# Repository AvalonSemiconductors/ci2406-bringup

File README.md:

# ci2406-bringup
Bring-up of CI2406 multi-project die.

[Documentation](https://avalonsemiconductors.github.io/CI2406/index.html)

[Tapeout repo](https://github.com/rejunity/ci2406-rej-pommedeterrible-tholin)

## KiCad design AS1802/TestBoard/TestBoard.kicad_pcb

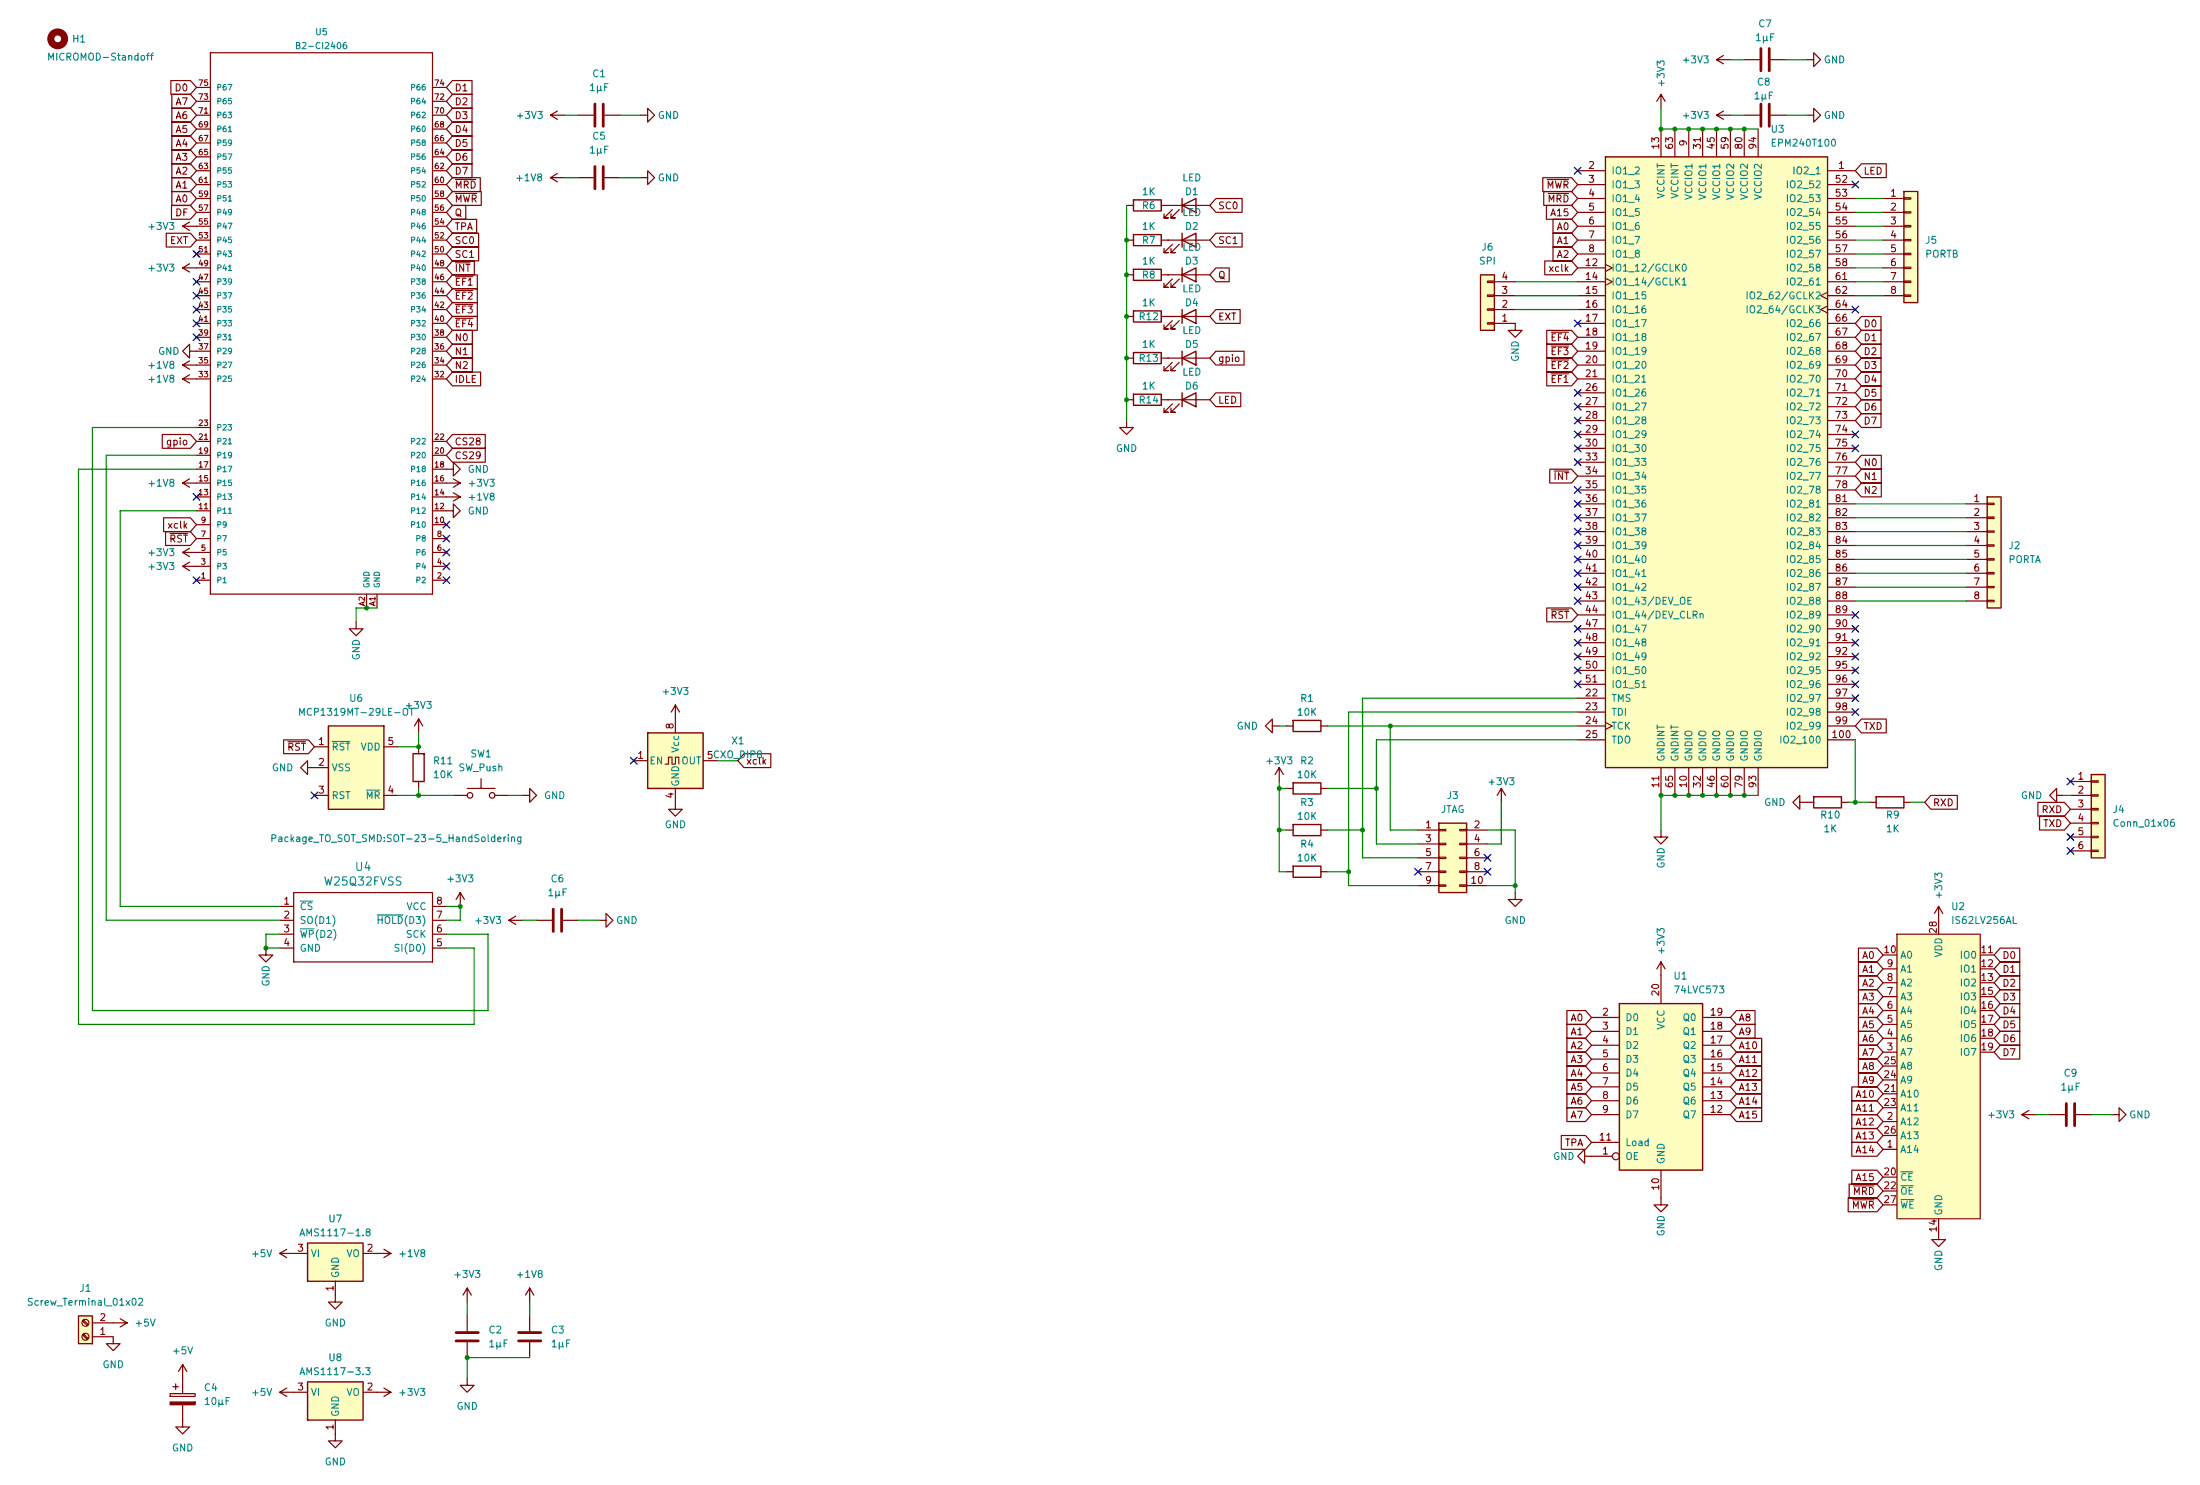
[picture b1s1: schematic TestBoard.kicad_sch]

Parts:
C1, C2, C3, C5, C6, C7, C8, C9: 1µF; C_0805_2012Metric_Pad1.18x1.45mm_HandSolder
C4: 10µF; CP_Radial_D4.0mm_P2.00mm
D1, D2, D3, D4, D5, D6: LED; LED_1206_3216Metric_Pad1.42x1.75mm_HandSolder
H1: MICROMOD-Standoff; MicroMod-Standoff
J1: Screw_Terminal_01x02; TerminalBlock_bornier-2_P5.08mm
J2: PORTA; PinHeader_1x08_P2.54mm_Vertical
J3: JTAG; PinHeader_2x05_P2.54mm_Vertical
J4: Conn_01x06; PinSocket_1x06_P2.54mm_Vertical
J5: PORTB; PinHeader_1x08_P2.54mm_Vertical
J6: SPI; PinHeader_1x04_P2.54mm_Vertical
R1, R2, R3, R4, R11: 10K; R_1206_3216Metric_Pad1.30x1.75mm_HandSolder
R6, R7, R8, R9, R10, R12, R13, R14: 1K; R_1206_3216Metric_Pad1.30x1.75mm_HandSolder
SW1: SW_Push; SW_PUSH_6mm
U1: 74LVC573; SO-20_12.8x7.5mm_P1.27mm
U2: IS62LV256AL; TSOP-I-28_11.8x8mm_P0.55mm-weird-pin-order
U3: EPM240T100; LQFP-100_14x14mm_P0.5mm
U4: W25Q32FVSS; DIP-8_W7.62mm; Part # W25Q32JVSSIQ
U5: B2-CI2406; M.2-CONNECTOR-E
U6: MCP1319MT-29LE-OT; SOT-23-5_HandSoldering
U7: AMS1117-1.8; SOT-223-3_TabPin2
U8: AMS1117-3.3; SOT-223-3_TabPin2
X1: CXO_DIP8; Oscillator_DIP-8

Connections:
+1V8: C3.2, C5.1, U5.14, U5.15, U5.33 (P25), U5.35 (P27), U7.2 (VO)
+3V3: C1.1, C2.2, C6.1, C7.1, C8.1, C9.1, J3.4, R2.2, R3.2, R4.2, R11.2, U1.20 (VCC), U2.28 (VDD), U3.9 (VCCIO1), U3.13 (VCCINT), U3.31 (VCCIO1), U3.45 (VCCIO1), U3.59 (VCCIO2), U3.63 (VCCINT), U3.80 (VCCIO2), U3.94 (VCCIO2), U4.7 (~HOLD(D3)), U4.8 (VCC), U5.3, U5.5, U5.16, U5.49 (P41), U5.55 (P47), U6.5 (VDD), U8.2 (VO), X1.8 (Vcc)
+5V: C4.1, J1.2, U7.3 (VI), U8.3 (VI)
A0: U1.2 (D0), U2.10 (A0), U3.6 (IO1_6), U5.59 (P51)
A1: U1.3 (D1), U2.9 (A1), U3.7 (IO1_7), U5.61 (P53)
A2: U1.4 (D2), U2.8 (A2), U3.8 (IO1_8), U5.63 (P55)
A3: U1.5 (D3), U2.7 (A3), U5.65 (P57)
A4: U1.6 (D4), U2.6 (A4), U5.67 (P59)
A5: U1.7 (D5), U2.5 (A5), U5.69 (P61)
A6: U1.8 (D6), U2.4 (A6), U5.71 (P63)
A7: U1.9 (D7), U2.3 (A7), U5.73 (P65)
A8: U1.19 (Q0), U2.25 (A8)
A9: U1.18 (Q1), U2.24 (A9)
A10: U1.17 (Q2), U2.21 (A10)
A11: U1.16 (Q3), U2.23 (A11)
A12: U1.15 (Q4), U2.2 (A12)
A13: U1.14 (Q5), U2.26 (A13)
A14: U1.13 (Q6), U2.1 (A14)
A15: U1.12 (Q7), U2.20 (~CE), U3.5 (IO1_5)
CS28: U5.22
CS29: U5.20
D0: U2.11 (IO0), U3.66 (IO2_66), U5.75 (P67)
D1: U2.12 (IO1), U3.67 (IO2_67), U5.74 (P66)
D2: U2.13 (IO2), U3.68 (IO2_68), U5.72 (P64)
D3: U2.15 (IO3), U3.69 (IO2_69), U5.70 (P62)
D4: U2.16 (IO4), U3.70 (IO2_70), U5.68 (P60)
D5: U2.17 (IO5), U3.71 (IO2_71), U5.66 (P58)
D6: U2.18 (IO6), U3.72 (IO2_72), U5.64 (P56)
D7: U2.19 (IO7), U3.73 (IO2_73), U5.62 (P54)
DF: U5.57 (P49)
EXT: D4.2 (A), U5.53 (P45)
GND: C1.2, C2.1, C3.1, C4.2, C5.2, C6.2, C7.2, C8.2, C9.2, J1.1, J3.2, J3.10, J4.2, J6.1, R1.2, R6.2, R7.2, R8.2, R10.2, R12.2, R13.2, R14.2, SW1.2, U1.1 (OE), U1.10 (GND), U2.14 (GND), U3.10 (GNDIO), U3.11 (GNDINT), U3.32 (GNDIO), U3.46 (GNDIO), U3.60 (GNDIO), U3.65 (GNDINT), U3.79 (GNDIO), U3.93 (GNDIO), U4.3 (~WP(D2)), U4.4 (GND), U5.12, U5.18, U5.37 (P29), U5.A1 (GND), U5.A2 (GND), U6.2 (VSS), U7.1 (GND), U8.1 (GND), X1.4 (GND)
IDLE: U5.32 (P24)
LED: D6.2 (A), U3.1 (IO2_1)
N0: U3.76 (IO2_76), U5.38 (P30)
N1: U3.77 (IO2_77), U5.36 (P28)
N2: U3.78 (IO2_78), U5.34 (P26)
unnamed: D1.1 (K), R6.1
unnamed: D2.1 (K), R7.1
unnamed: D3.1 (K), R8.1
unnamed: D4.1 (K), R12.1
unnamed: D5.1 (K), R13.1
unnamed: D6.1 (K), R14.1
unnamed: J2.1, U3.81 (IO2_81)
unnamed: J2.2, U3.82 (IO2_82)
unnamed: J2.3, U3.83 (IO2_83)
unnamed: J2.4, U3.84 (IO2_84)
unnamed: J2.5, U3.85 (IO2_85)
unnamed: J2.6, U3.86 (IO2_86)
unnamed: J2.7, U3.87 (IO2_87)
unnamed: J2.8, U3.88 (IO2_88)
unnamed: J3.1, R1.1, U3.24 (TCK)
unnamed: J3.3, R2.1, U3.25 (TDO)
unnamed: J3.5, R3.1, U3.22 (TMS)
unnamed: J3.9, R4.1, U3.23 (TDI)
unnamed: J5.1, U3.53 (IO2_53)
unnamed: J5.2, U3.54 (IO2_54)
unnamed: J5.3, U3.55 (IO2_55)
unnamed: J5.4, U3.56 (IO2_56)
unnamed: J5.5, U3.57 (IO2_57)
unnamed: J5.6, U3.58 (IO2_58)
unnamed: J5.7, U3.61 (IO2_61)
unnamed: J5.8, U3.62 (IO2_62/GCLK2)
unnamed: J6.2, U3.16 (IO1_16)
unnamed: J6.3, U3.15 (IO1_15)
unnamed: J6.4, U3.14 (IO1_14/GCLK1)
unnamed: R9.2, R10.1, U3.100 (IO2_100)
unnamed: U4.6 (SCK), U5.23
unnamed: U4.5 (SI(D0)), U5.17
unnamed: U4.2 (SO(D1)), U5.19
unnamed: U4.1 (~CS), U5.11
unnamed: R11.1, SW1.1, U6.4 (~MR)
Q: D3.2 (A), U5.56 (P48)
RXD: J4.3, R9.1
SC0: D1.2 (A), U5.52 (P44)
SC1: D2.2 (A), U5.50 (P42)
TPA: U1.11 (Load), U5.54 (P46)
TXD: J4.4, U3.99 (IO2_99)
gpio: D5.2 (A), U5.21
xclk: U3.12 (IO1_12/GCLK0), U5.9, X1.5 (OUT)
~EF1: U3.21 (IO1_21), U5.46 (P38)
~EF2: U3.20 (IO1_20), U5.44 (P36)
~EF3: U3.19 (IO1_19), U5.42 (P34)
~EF4: U3.18 (IO1_18), U5.40 (P32)
~INT: U3.34 (IO1_34), U5.48 (P40)
~MRD: U2.22 (~OE), U3.4 (IO1_4), U5.60 (P52)
~MWR: U2.27 (~WE), U3.3 (IO1_3), U5.58 (P50)
~RST: U3.44 (IO1_44/DEV_CLRn), U5.7, U6.1 (~RST)

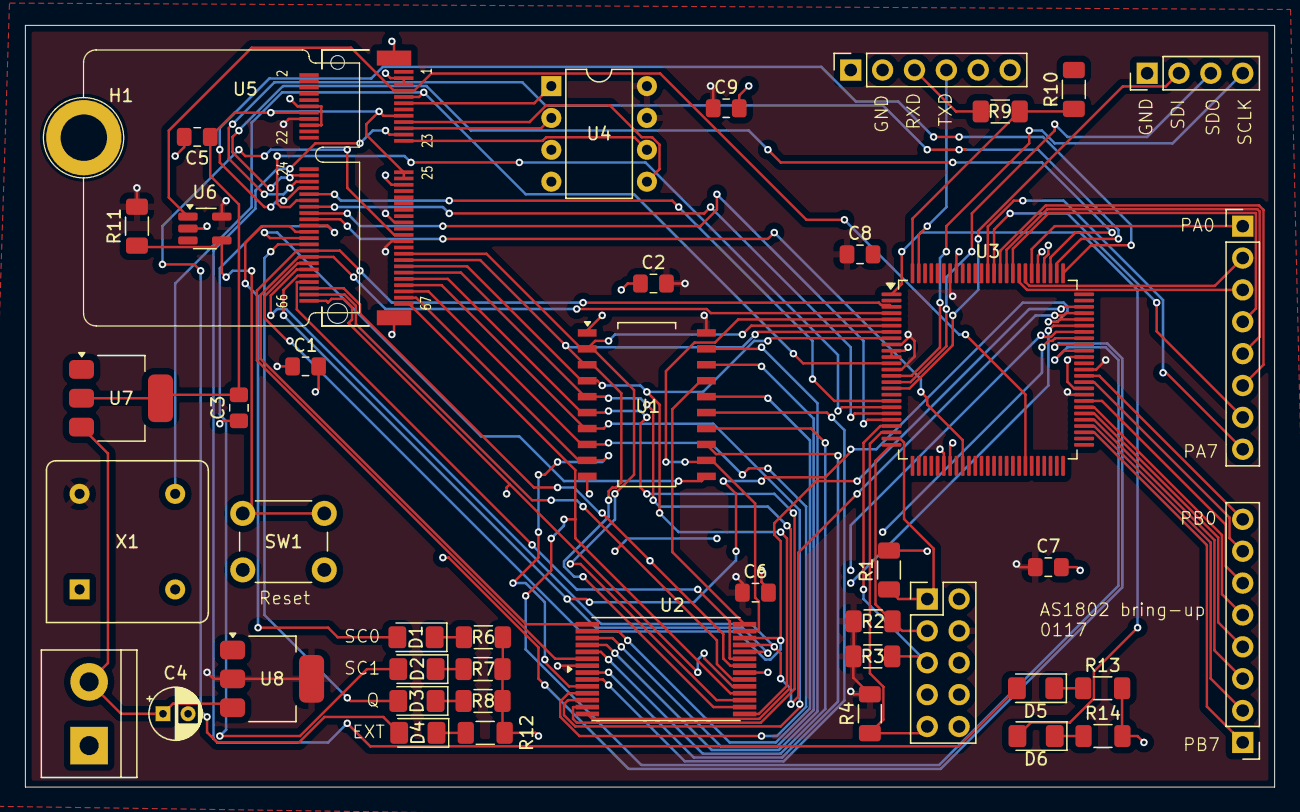
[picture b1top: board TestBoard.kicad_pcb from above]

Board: 4 copper layers, 99.6 x 60.7 mm, 45 parts (0 on the bottom side), 84 nets.

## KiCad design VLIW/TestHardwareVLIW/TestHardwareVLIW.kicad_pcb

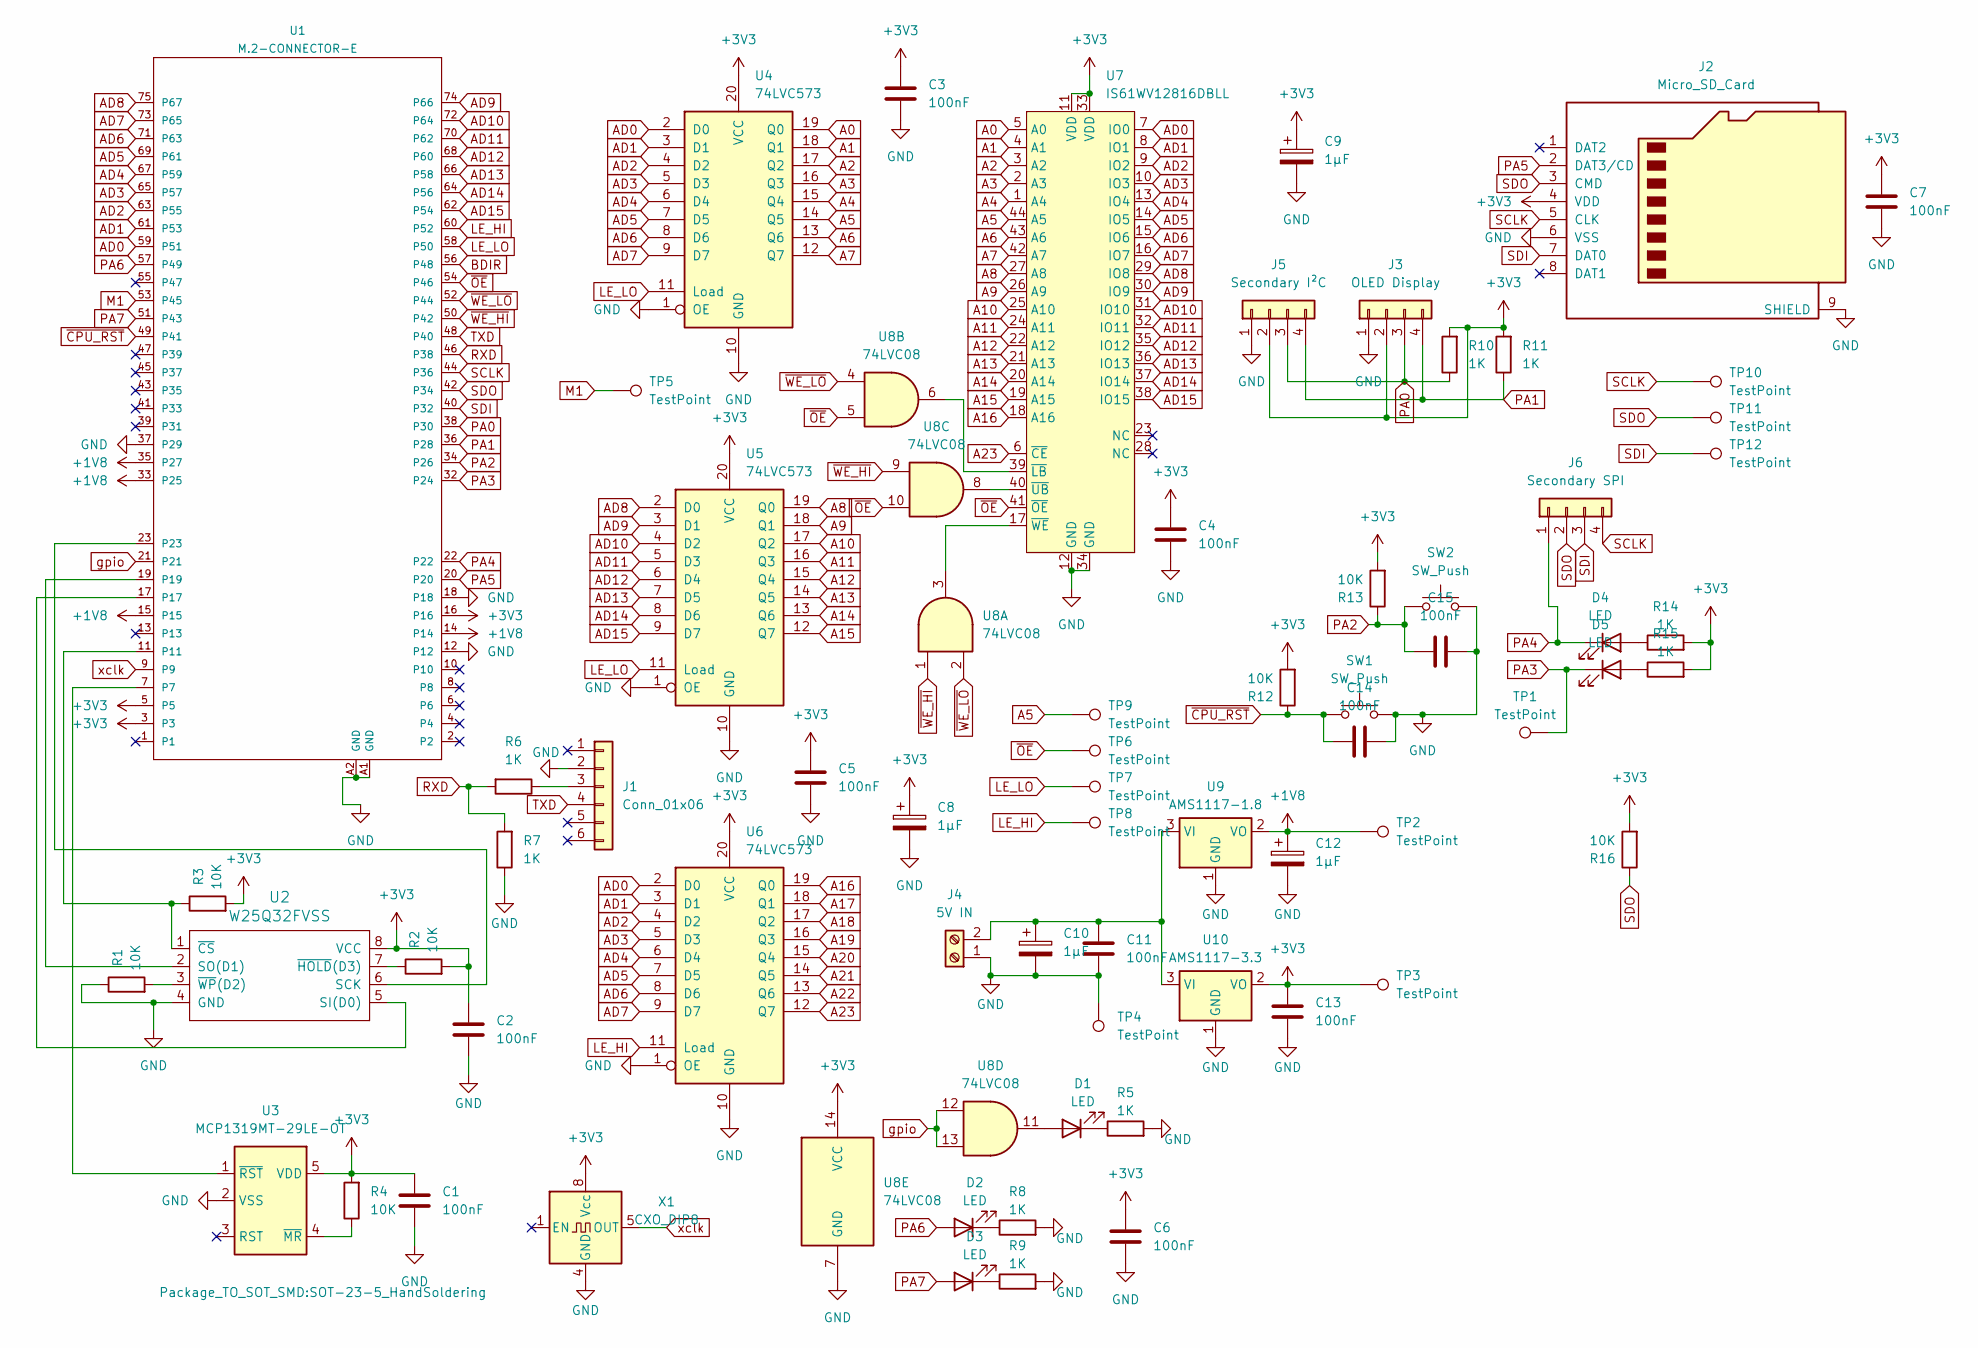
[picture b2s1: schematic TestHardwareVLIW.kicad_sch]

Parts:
C1, C2, C3, C4, C5, C6, C7, C11, C13, C14, C15: 100nF; C_0805_2012Metric_Pad1.18x1.45mm_HandSolder
C8, C9, C10, C12: 1µF; CP_Radial_D4.0mm_P2.00mm
D1, D2, D3, D4, D5: LED; LED_1206_3216Metric_Pad1.42x1.75mm_HandSolder
J1: Conn_01x06; PinSocket_1x06_P2.54mm_Vertical
J2: Micro_SD_Card; microSD_HC_Hirose_DM3AT-SF-PEJM5
J3: OLED Display; PinSocket_1x04_P2.54mm_Vertical
J4: 5V IN; TerminalBlock_bornier-2_P5.08mm
J5: Secondary I²C; PinSocket_1x04_P2.54mm_Vertical
J6: Secondary SPI; PinSocket_1x04_P2.54mm_Vertical
R1, R2, R3, R12, R13, R16: 10K; R_1206_3216Metric_Pad1.30x1.75mm_HandSolder; Part # RC0805FR-0710KL
R4: 10K; R_1206_3216Metric_Pad1.30x1.75mm_HandSolder
R5, R6, R7, R8, R9, R10, R11, R14, R15: 1K; R_1206_3216Metric_Pad1.30x1.75mm_HandSolder
SW1, SW2: SW_Push; SW_PUSH_6mm
TP1, TP2, TP3, TP4, TP5, TP6, TP7, TP8, TP9, TP10, TP11, TP12: TestPoint; TestPoint_Pad_D1.0mm
U1: M.2-CONNECTOR-E
U2: W25Q32FVSS; DIP-8_W7.62mm; Part # W25Q32JVSSIQ
U3: MCP1319MT-29LE-OT; SOT-23-5_HandSoldering
U4, U5, U6: 74LVC573; TSSOP-20_4.4x6.5mm_P0.65mm
U7: IS61WV12816DBLL; TSOP-II-44_10.16x18.41mm_P0.8mm
U8: 74LVC08; SO-14_3.9x8.65mm_P1.27mm
U9: AMS1117-1.8; SOT-223-3_TabPin2
U10: AMS1117-3.3; SOT-223-3_TabPin2
X1: CXO_DIP8; Oscillator_DIP-8

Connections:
+1V8: C12.1, TP2.1, U1.14, U1.15, U1.33 (P25), U1.35 (P27), U9.2 (VO)
+3V3: C1.1, C2.1, C3.1, C4.1, C5.1, C6.1, C7.1, C8.1, C9.1, C13.1, J2.4 (VDD), J3.2, J5.2, R2.2, R3.2, R4.2, R10.2, R11.2, R12.2, R13.2, R14.2, R15.2, R16.2, TP3.1, U1.3, U1.5, U1.16, U2.8 (VCC), U3.5 (VDD), U4.20 (VCC), U5.20 (VCC), U6.20 (VCC), U7.11 (VDD), U7.33 (VDD), U8.14 (VCC), U10.2 (VO), X1.8 (Vcc)
A0: U4.19 (Q0), U7.5 (A0)
A1: U4.18 (Q1), U7.4 (A1)
A2: U4.17 (Q2), U7.3 (A2)
A3: U4.16 (Q3), U7.2 (A3)
A4: U4.15 (Q4), U7.1 (A4)
A5: TP9.1, U4.14 (Q5), U7.44 (A5)
A6: U4.13 (Q6), U7.43 (A6)
A7: U4.12 (Q7), U7.42 (A7)
A8: U5.19 (Q0), U7.27 (A8)
A9: U5.18 (Q1), U7.26 (A9)
A10: U5.17 (Q2), U7.25 (A10)
A11: U5.16 (Q3), U7.24 (A11)
A12: U5.15 (Q4), U7.22 (A12)
A13: U5.14 (Q5), U7.21 (A13)
A14: U5.13 (Q6), U7.20 (A14)
A15: U5.12 (Q7), U7.19 (A15)
A16: U6.19 (Q0), U7.18 (A16)
A17: U6.18 (Q1)
A18: U6.17 (Q2)
A19: U6.16 (Q3)
A20: U6.15 (Q4)
A21: U6.14 (Q5)
A22: U6.13 (Q6)
A23: U6.12 (Q7), U7.6 (~CE)
AD0: U1.59 (P51), U4.2 (D0), U6.2 (D0), U7.7 (IO0)
AD1: U1.61 (P53), U4.3 (D1), U6.3 (D1), U7.8 (IO1)
AD2: U1.63 (P55), U4.4 (D2), U6.4 (D2), U7.9 (IO2)
AD3: U1.65 (P57), U4.5 (D3), U6.5 (D3), U7.10 (IO3)
AD4: U1.67 (P59), U4.6 (D4), U6.6 (D4), U7.13 (IO4)
AD5: U1.69 (P61), U4.7 (D5), U6.7 (D5), U7.14 (IO5)
AD6: U1.71 (P63), U4.8 (D6), U6.8 (D6), U7.15 (IO6)
AD7: U1.73 (P65), U4.9 (D7), U6.9 (D7), U7.16 (IO7)
AD8: U1.75 (P67), U5.2 (D0), U7.29 (IO8)
AD9: U1.74 (P66), U5.3 (D1), U7.30 (IO9)
AD10: U1.72 (P64), U5.4 (D2), U7.31 (IO10)
AD11: U1.70 (P62), U5.5 (D3), U7.32 (IO11)
AD12: U1.68 (P60), U5.6 (D4), U7.35 (IO12)
AD13: U1.66 (P58), U5.7 (D5), U7.36 (IO13)
AD14: U1.64 (P56), U5.8 (D6), U7.37 (IO14)
AD15: U1.62 (P54), U5.9 (D7), U7.38 (IO15)
BDIR: U1.56 (P48)
GND: C1.2, C2.2, C3.2, C4.2, C5.2, C6.2, C7.2, C8.2, C9.2, C10.2, C11.2, C12.2, C13.2, C14.1, C15.1, J1.2, J2.6 (VSS), J2.9 (SHIELD), J3.1, J4.1, J5.1, R1.1, R5.2, R7.1, R8.2, R9.2, SW1.2, SW2.2, TP4.1, U1.12, U1.18, U1.37 (P29), U1.A1 (GND), U1.A2 (GND), U2.4 (GND), U3.2 (VSS), U4.1 (OE), U4.10 (GND), U5.1 (OE), U5.10 (GND), U6.1 (OE), U6.10 (GND), U7.12 (GND), U7.34 (GND), U8.7 (GND), U9.1 (GND), U10.1 (GND), X1.4 (GND)
LE_HI: TP8.1, U1.60 (P52), U6.11 (Load)
LE_LO: TP7.1, U1.58 (P50), U4.11 (Load), U5.11 (Load)
M1: TP5.1, U1.53 (P45)
unnamed: D1.2 (A), U8.11
unnamed: D1.1 (K), R5.1
unnamed: D2.1 (K), R8.1
unnamed: D3.1 (K), R9.1
unnamed: D4.2 (A), R14.1
unnamed: D5.2 (A), R15.1
unnamed: J1.3, R6.1
unnamed: C10.1, C11.1, J4.2, U9.3 (VI), U10.3 (VI)
unnamed: U1.7, U3.1 (~RST)
unnamed: R3.1, U1.11, U2.1 (~CS)
unnamed: U1.17, U2.5 (SI(D0))
unnamed: U1.19, U2.2 (SO(D1))
unnamed: U1.23, U2.6 (SCK)
unnamed: R2.1, U2.7 (~HOLD(D3))
unnamed: R1.2, U2.3 (~WP(D2))
unnamed: R4.1, U3.4 (~MR)
unnamed: U7.39 (~LB), U8.6
unnamed: U7.40 (~UB), U8.8
unnamed: U7.17 (~WE), U8.3
PA0: J3.3, J5.3, R10.1, U1.38 (P30)
PA1: J3.4, J5.4, R11.1, U1.36 (P28)
PA2: C15.2, R13.1, SW2.1, U1.34 (P26)
PA3: D5.1 (K), TP1.1, U1.32 (P24)
PA4: D4.1 (K), J6.1, U1.22
PA5: J2.2 (DAT3/CD), U1.20
PA6: D2.2 (A), U1.57 (P49)
PA7: D3.2 (A), U1.51 (P43)
RXD: R6.2, R7.2, U1.46 (P38)
SCLK: J2.5 (CLK), J6.4, TP10.1, U1.44 (P36)
SDI: J2.7 (DAT0), J6.3, TP12.1, U1.40 (P32)
SDO: J2.3 (CMD), J6.2, R16.1, TP11.1, U1.42 (P34)
TXD: J1.4, U1.48 (P40)
gpio: U1.21, U8.12, U8.13
xclk: U1.9, X1.5 (OUT)
~CPU_RST: C14.2, R12.1, SW1.1, U1.49 (P41)
~OE: TP6.1, U1.54 (P46), U7.41 (~OE), U8.5, U8.10
~WE_HI: U1.50 (P42), U8.1, U8.9
~WE_LO: U1.52 (P44), U8.2, U8.4

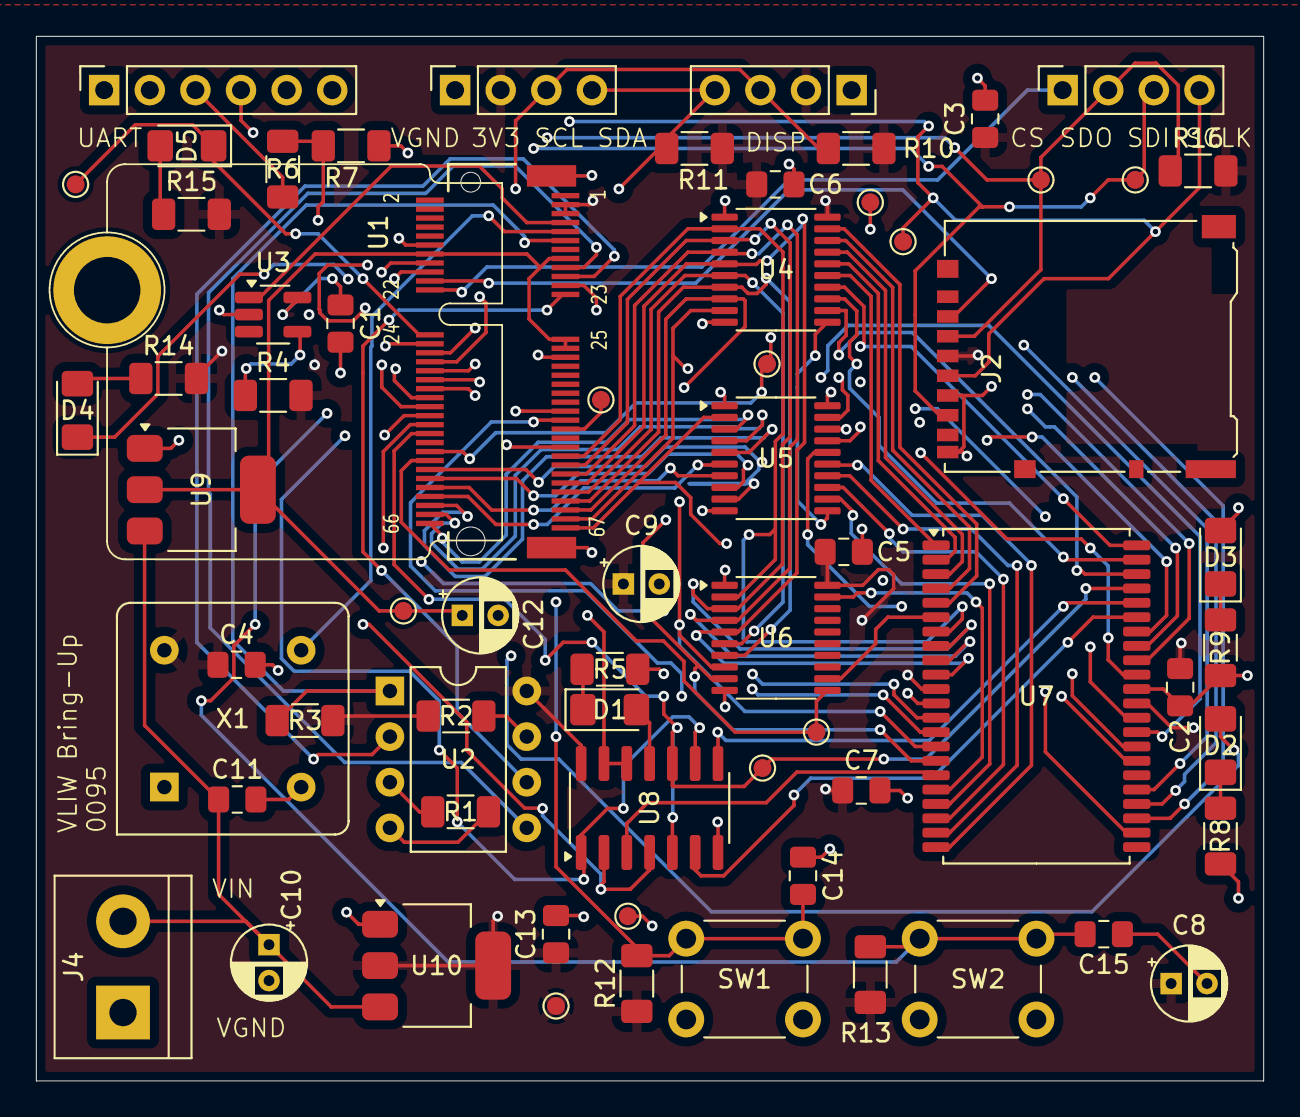
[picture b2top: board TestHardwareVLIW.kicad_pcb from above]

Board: 4 copper layers, 68.3 x 58.2 mm, 67 parts (0 on the bottom side), 78 nets.

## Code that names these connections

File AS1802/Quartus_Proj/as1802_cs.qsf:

# -------------------------------------------------------------------------- #
#
# Copyright (C) 2025  Altera Corporation. All rights reserved.
# Your use of Altera Corporation's design tools, logic functions 
# and other software and tools, and any partner logic 
# functions, and any output files from any of the foregoing 
# (including device programming or simulation files), and any 
# associated documentation or information are expressly subject 
# to the terms and conditions of the Altera Program License 
# Subscription Agreement, the Altera Quartus Prime License Agreement,
# the Altera IP License Agreement, or other applicable license
# agreement, including, without limitation, that your use is for
# the sole purpose of programming logic devices manufactured by
# Altera and sold by Altera or its authorized distributors.  Please
# refer to the Altera Software License Subscription Agreements 
# on the Quartus Prime software download page.
#
# -------------------------------------------------------------------------- #
#
# Quartus Prime
# Version 24.1std.0 Build 1077 03/04/2025 SC Lite Edition
# Date created = 18:14:34  Mai 04, 2025
#
# -------------------------------------------------------------------------- #
#
# Notes:
#
# 1) The default values for assignments are stored in the file:
#		as1802_cs_assignment_defaults.qdf
#    If this file doesn't exist, see file:
#		assignment_defaults.qdf
#
# 2) Intel recommends that you do not modify this file. This
#    file is updated automatically by the Quartus Prime software
#    and any changes you make may be lost or overwritten.
#
# -------------------------------------------------------------------------- #


set_global_assignment -name FAMILY "MAX II"
set_global_assignment -name DEVICE EPM240T100C5
set_global_assignment -name TOP_LEVEL_ENTITY as1802_cs
set_global_assignment -name ORIGINAL_QUARTUS_VERSION 24.1STD.0
set_global_assignment -name PROJECT_CREATION_TIME_DATE "18:14:34  MAI 04, 2025"
set_global_assignment -name LAST_QUARTUS_VERSION "24.1std.0 Lite Edition"
set_global_assignment -name PROJECT_OUTPUT_DIRECTORY output_files
set_global_assignment -name MIN_CORE_JUNCTION_TEMP 0
set_global_assignment -name MAX_CORE_JUNCTION_TEMP 85
set_global_assignment -name DEVICE_FILTER_PACKAGE TQFP
set_global_assignment -name DEVICE_FILTER_PIN_COUNT 100
set_global_assignment -name ERROR_CHECK_FREQUENCY_DIVISOR "-1"
set_global_assignment -name POWER_EXT_SUPPLY_VOLTAGE_TO_REGULATOR 3.3V
set_global_assignment -name VERILOG_FILE cpld.v
set_global_assignment -name AUTO_RESTART_CONFIGURATION OFF
set_global_assignment -name ENABLE_DEVICE_WIDE_RESET ON
set_global_assignment -name ENABLE_OCT_DONE OFF
set_global_assignment -name ENABLE_CONFIGURATION_PINS OFF
set_global_assignment -name ENABLE_BOOT_SEL_PIN OFF
set_global_assignment -name USE_CONFIGURATION_DEVICE ON
set_global_assignment -name RESERVE_ALL_UNUSED_PINS "AS INPUT TRI-STATED WITH WEAK PULL-UP"
set_location_assignment PIN_5 -to A15
set_location_assignment PIN_73 -to D[7]
set_location_assignment PIN_72 -to D[6]
set_location_assignment PIN_71 -to D[5]
set_location_assignment PIN_70 -to D[4]
set_location_assignment PIN_69 -to D[3]
set_location_assignment PIN_68 -to D[2]
set_location_assignment PIN_67 -to D[1]
set_location_assignment PIN_66 -to D[0]
set_location_assignment PIN_18 -to EF_b[3]
set_location_assignment PIN_19 -to EF_b[2]
set_location_assignment PIN_20 -to EF_b[1]
set_location_assignment PIN_21 -to EF_b[0]
set_location_assignment PIN_1 -to LED
set_location_assignment PIN_4 -to MRD_b
set_location_assignment PIN_3 -to MWR_b
set_location_assignment PIN_26 -to N[2]
set_location_assignment PIN_27 -to N[1]
set_location_assignment PIN_28 -to N[0]
set_location_assignment PIN_88 -to PORTA[7]
set_location_assignment PIN_87 -to PORTA[6]
set_location_assignment PIN_86 -to PORTA[5]
set_location_assignment PIN_85 -to PORTA[4]
set_location_assignment PIN_84 -to PORTA[3]
set_location_assignment PIN_83 -to PORTA[2]
set_location_assignment PIN_82 -to PORTA[1]
set_location_assignment PIN_81 -to PORTA[0]
set_location_assignment PIN_53 -to PORTB[7]
set_location_assignment PIN_54 -to PORTB[6]
set_location_assignment PIN_55 -to PORTB[5]
set_location_assignment PIN_56 -to PORTB[4]
set_location_assignment PIN_57 -to PORTB[3]
set_location_assignment PIN_58 -to PORTB[2]
set_location_assignment PIN_61 -to PORTB[1]
set_location_assignment PIN_62 -to PORTB[0]
set_location_assignment PIN_100 -to RXD
set_location_assignment PIN_99 -to TXD
set_location_assignment PIN_14 -to SCK
set_location_assignment PIN_16 -to SDI
set_location_assignment PIN_15 -to SDO
set_location_assignment PIN_8 -to addr[2]
set_location_assignment PIN_7 -to addr[1]
set_location_assignment PIN_6 -to addr[0]
set_location_assignment PIN_34 -to int_b
set_location_assignment PIN_12 -to xclk

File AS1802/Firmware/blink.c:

#include <defs.h>
#include "../Programs/BringUpSample/pgmdata.h"

#define reg_mprj_proj_sel (*(volatile uint32_t*)0x30100004)
#define reg_mprj_counter  (*(volatile uint32_t*)0x30100008)
#define reg_mprj_settings (*(volatile uint32_t*)0x3010000C)

#define START_ADDRESS 0
#define START_X 1
#define START_P 0
#define GATE_TPA 1
#define CS 1

#define MRD (1 << 21)
#define MWR (1 << 22)
#define Q_L (1 << 23)
#define TPA (1 << 24)


void delay(const int d) {
	#ifdef BROKEN_CHIP
	for(int i = 0; i < d >> 2; i++) asm volatile("nop");
	#else
	reg_timer0_config = 0;
	reg_timer0_data = d;
	reg_timer0_config = 1;
	
	reg_timer0_update = 1;
	while (reg_timer0_value > 0) {
		reg_timer0_update = 1;
	}
	#endif
}

uint32_t datal_shadow;

void configure_io_mgmt(uint8_t input) {
	reg_mprj_io_0 = GPIO_MODE_USER_STD_INPUT_PULLDOWN;
	reg_mprj_io_1 = GPIO_MODE_MGMT_STD_OUTPUT;
	reg_mprj_io_2 = GPIO_MODE_MGMT_STD_OUTPUT;
	reg_mprj_io_3 = GPIO_MODE_MGMT_STD_INPUT_PULLUP;
	reg_mprj_io_4 = GPIO_MODE_MGMT_STD_OUTPUT;
	
	reg_mprj_io_5 = GPIO_MODE_MGMT_STD_OUTPUT;
	reg_mprj_io_6 = GPIO_MODE_MGMT_STD_OUTPUT;
	reg_mprj_io_7 = GPIO_MODE_MGMT_STD_OUTPUT;
	reg_mprj_io_8 = GPIO_MODE_MGMT_STD_OUTPUT;
	reg_mprj_io_9 = GPIO_MODE_MGMT_STD_OUTPUT;
	reg_mprj_io_10 = GPIO_MODE_MGMT_STD_OUTPUT;
	reg_mprj_io_11 = GPIO_MODE_MGMT_STD_OUTPUT;
	reg_mprj_io_12 = GPIO_MODE_MGMT_STD_OUTPUT;
	if(input) {
		reg_mprj_io_13 = GPIO_MODE_MGMT_STD_INPUT_PULLUP;
		reg_mprj_io_14 = GPIO_MODE_MGMT_STD_INPUT_PULLUP;
		reg_mprj_io_15 = GPIO_MODE_MGMT_STD_INPUT_PULLUP;
		reg_mprj_io_16 = GPIO_MODE_MGMT_STD_INPUT_PULLUP;
		reg_mprj_io_17 = GPIO_MODE_MGMT_STD_INPUT_PULLUP;
		reg_mprj_io_18 = GPIO_MODE_MGMT_STD_INPUT_PULLUP;
		reg_mprj_io_19 = GPIO_MODE_MGMT_STD_INPUT_PULLUP;
		reg_mprj_io_20 = GPIO_MODE_MGMT_STD_INPUT_PULLUP;
	}else {
		reg_mprj_io_13 = GPIO_MODE_MGMT_STD_OUTPUT;
		reg_mprj_io_14 = GPIO_MODE_MGMT_STD_OUTPUT;
		reg_mprj_io_15 = GPIO_MODE_MGMT_STD_OUTPUT;
		reg_mprj_io_16 = GPIO_MODE_MGMT_STD_OUTPUT;
		reg_mprj_io_17 = GPIO_MODE_MGMT_STD_OUTPUT;
		reg_mprj_io_18 = GPIO_MODE_MGMT_STD_OUTPUT;
		reg_mprj_io_19 = GPIO_MODE_MGMT_STD_OUTPUT;
		reg_mprj_io_20 = GPIO_MODE_MGMT_STD_OUTPUT;
	}
	reg_mprj_io_21 = GPIO_MODE_MGMT_STD_OUTPUT;
	reg_mprj_io_22 = GPIO_MODE_MGMT_STD_OUTPUT;
	reg_mprj_io_23 = GPIO_MODE_MGMT_STD_OUTPUT;
	reg_mprj_io_24 = GPIO_MODE_MGMT_STD_OUTPUT;
	reg_mprj_io_25 = GPIO_MODE_MGMT_STD_OUTPUT;
	reg_mprj_io_26 = GPIO_MODE_MGMT_STD_INPUT_NOPULL;
	reg_mprj_io_27 = GPIO_MODE_MGMT_STD_INPUT_PULLUP;
	reg_mprj_io_28 = GPIO_MODE_MGMT_STD_INPUT_PULLUP;
	reg_mprj_io_29 = GPIO_MODE_MGMT_STD_INPUT_PULLUP;
	reg_mprj_io_30 = GPIO_MODE_MGMT_STD_INPUT_PULLUP;
	reg_mprj_io_31 = GPIO_MODE_MGMT_STD_INPUT_PULLUP;
	reg_mprj_io_32 = GPIO_MODE_MGMT_STD_OUTPUT;
	reg_mprj_io_33 = GPIO_MODE_MGMT_STD_OUTPUT;
	reg_mprj_io_34 = GPIO_MODE_MGMT_STD_OUTPUT;
	reg_mprj_io_35 = GPIO_MODE_MGMT_STD_OUTPUT;
	reg_mprj_io_36 = GPIO_MODE_MGMT_STD_OUTPUT;
	reg_mprj_io_37 = GPIO_MODE_MGMT_STD_OUTPUT;
	
	reg_mprj_datal = datal_shadow = MRD | MWR;
	reg_mprj_datah = 0xFFFFFFFF;
	reg_mprj_xfer = 1;
	while(reg_mprj_xfer == 1);
}

void configure_io_as1802() {
	reg_mprj_io_0 = GPIO_MODE_USER_STD_INPUT_PULLDOWN;
	reg_mprj_io_1 = GPIO_MODE_USER_STD_OUTPUT;
	reg_mprj_io_2 = GPIO_MODE_USER_STD_OUTPUT;
	reg_mprj_io_3 = GPIO_MODE_MGMT_STD_INPUT_PULLUP;
	reg_mprj_io_4 = GPIO_MODE_USER_STD_OUTPUT;
	
	reg_mprj_io_5 = GPIO_MODE_USER_STD_OUTPUT;
	reg_mprj_io_6 = GPIO_MODE_USER_STD_OUTPUT;
	reg_mprj_io_7 = GPIO_MODE_USER_STD_OUTPUT;
	reg_mprj_io_8 = GPIO_MODE_USER_STD_OUTPUT;
	reg_mprj_io_9 = GPIO_MODE_USER_STD_OUTPUT;
	reg_mprj_io_10 = GPIO_MODE_USER_STD_OUTPUT;
	reg_mprj_io_11 = GPIO_MODE_USER_STD_OUTPUT;
	reg_mprj_io_12 = GPIO_MODE_USER_STD_OUTPUT;
	reg_mprj_io_13 = GPIO_MODE_USER_STD_BIDIRECTIONAL;
	reg_mprj_io_14 = GPIO_MODE_USER_STD_BIDIRECTIONAL;
	reg_mprj_io_15 = GPIO_MODE_USER_STD_BIDIRECTIONAL;
	reg_mprj_io_16 = GPIO_MODE_USER_STD_BIDIRECTIONAL;
	reg_mprj_io_17 = GPIO_MODE_USER_STD_BIDIRECTIONAL;
	reg_mprj_io_18 = GPIO_MODE_USER_STD_BIDIRECTIONAL;
	reg_mprj_io_19 = GPIO_MODE_USER_STD_BIDIRECTIONAL;
	reg_mprj_io_20 = GPIO_MODE_USER_STD_BIDIRECTIONAL;
	reg_mprj_io_21 = GPIO_MODE_USER_STD_OUTPUT;
	reg_mprj_io_22 = GPIO_MODE_USER_STD_OUTPUT;
	reg_mprj_io_23 = GPIO_MODE_USER_STD_OUTPUT;
	reg_mprj_io_24 = GPIO_MODE_USER_STD_OUTPUT;
	reg_mprj_io_25 = GPIO_MODE_USER_STD_OUTPUT;
	reg_mprj_io_26 = GPIO_MODE_USER_STD_OUTPUT;
	reg_mprj_io_27 = GPIO_MODE_USER_STD_INPUT_PULLUP;
	reg_mprj_io_28 = GPIO_MODE_USER_STD_INPUT_PULLUP;
	reg_mprj_io_29 = GPIO_MODE_USER_STD_INPUT_PULLUP;
	reg_mprj_io_30 = GPIO_MODE_USER_STD_INPUT_PULLUP;
	reg_mprj_io_31 = GPIO_MODE_USER_STD_INPUT_PULLUP;
	reg_mprj_io_32 = GPIO_MODE_USER_STD_OUTPUT;
	reg_mprj_io_33 = GPIO_MODE_USER_STD_OUTPUT;
	reg_mprj_io_34 = GPIO_MODE_USER_STD_OUTPUT;
	reg_mprj_io_35 = GPIO_MODE_USER_STD_OUTPUT;
	reg_mprj_io_36 = GPIO_MODE_USER_STD_OUTPUT;
	reg_mprj_io_37 = GPIO_MODE_USER_STD_OUTPUT;
	
	reg_mprj_xfer = 1;
	while(reg_mprj_xfer == 1);
}

void set_addr(uint16_t addr) {
	datal_shadow &= ~(0xFF << 5);
	reg_mprj_datal = datal_shadow | ((uint32_t)(addr >> 8) << 5);
	reg_mprj_datal = datal_shadow | ((uint32_t)(addr >> 8) << 5) | TPA | Q_L;
	reg_mprj_datal = datal_shadow | ((uint32_t)(addr >> 8) << 5);
	reg_mprj_datal = datal_shadow = datal_shadow | ((uint32_t)(addr & 0xFF) << 5);
}

void set_data(uint8_t data) {
	datal_shadow &= ~(0xFF << 13);
	reg_mprj_datal = datal_shadow = datal_shadow | ((uint32_t)data << 13);
}

uint8_t get_data() {
	return (reg_mprj_datal >> 13) & 0xFF;
}

void error_out() {
	while(1) {
		reg_gpio_out = 1;
		delay(1000000);
		reg_gpio_out = 0;
		delay(70000);
	}
}

void main() {
	reg_uart_enable = 0;
	reg_spi_enable = 0;
	reg_wb_enable = 1;
	configure_io_mgmt(0);
	reg_gpio_mode1 = 1;
	reg_gpio_mode0 = 0;
	reg_gpio_ien = 1;
	reg_gpio_oe = 1;
	reg_gpio_out = 0;

	reg_mprj_proj_sel = 0b10001;
	//Cache bug workaround
	asm volatile("nop");
	asm volatile("nop");
	asm volatile("nop");
	asm volatile("nop");
	asm volatile("nop");
	asm volatile("nop");
	asm volatile("nop");
	asm volatile("nop");
	asm volatile("nop");
	asm volatile("nop");
	asm volatile("nop");
	asm volatile("nop");
	asm volatile("nop");
	asm volatile("nop");
	asm volatile("nop");
	asm volatile("nop");
	asm volatile("nop");
	asm volatile("nop");
	asm volatile("nop");
	asm volatile("nop");
	asm volatile("nop");
	asm volatile("nop");
	asm volatile("nop");
	reg_mprj_settings = START_ADDRESS | (START_X << 16) | (START_P <<  20) | (2 << 24) | (GATE_TPA << 26) | (1 << 27) | (CS << 28);
	//Cache bug workaround
	asm volatile("nop");
	asm volatile("nop");
	asm volatile("nop");
	asm volatile("nop");
	asm volatile("nop");
	asm volatile("nop");
	asm volatile("nop");
	asm volatile("nop");
	asm volatile("nop");
	asm volatile("nop");
	asm volatile("nop");
	asm volatile("nop");
	asm volatile("nop");
	asm volatile("nop");
	asm volatile("nop");
	asm volatile("nop");
	asm volatile("nop");
	asm volatile("nop");
	asm volatile("nop");
	asm volatile("nop");
	asm volatile("nop");
	asm volatile("nop");
	asm volatile("nop");
	
	uint32_t val = 0xAAAAAAAA;
	
	configure_io_mgmt(0);
	
	for(uint32_t i = 0; i < pgm_len; i++) {
		val = pgm[i >> 1];
		if((i & 1) != 0) val >>= 8;
		set_addr(i);
		set_data(val & 0xFF);
		reg_mprj_datal = datal_shadow & ~MWR;
		reg_mprj_datal = datal_shadow;
	}
	set_data(0);
	configure_io_mgmt(1);
	for(uint32_t i = 0; i < pgm_len; i++) {
		val = pgm[i >> 1];
		if((i & 1) != 0) val >>= 8;
		set_addr(i);
		reg_mprj_datal = datal_shadow & ~MRD;
		if(get_data() != (val & 0xFF)) {
			reg_mprj_datal = datal_shadow;
			error_out();
		}
		reg_mprj_datal = datal_shadow;
	}
	
	configure_io_as1802();
	reg_mprj_settings = 0x04000000;
	reg_mprj_proj_sel = 0b10111;
	reg_gpio_out = 0;
    
    while(1) {
		reg_gpio_out = 1;
		delay(40000000);
		reg_gpio_out = 0;
		delay(28000000);
	}
}

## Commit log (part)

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2025-06-21 Change README
2025-08-11 VLIW ext4 progress
2025-08-12 ext4 code done
2025-08-17 AS1802 bring-up
2025-10-02 Minor tweaks
